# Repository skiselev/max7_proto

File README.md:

# MAX7 Proto
Prototyping Board for Altera MAX7000 CPLDs

## Table of Content
* [Introduction](#introduction)
* [Hardware Documentation](#hardware-documentation)
  * [Schematic and PCB Layout](#schematic-and-pcb-layout)
  * [Connectors and Jumpers](#connectors-and-jumpers)
  * [Bill of Materials](#bill-of-materials)
* [Programming](#programming)

## Introduction

MAX7 Proto is a prototyping board based on Altera MAX7000 series CPLDs. The board has pin headers on both sides, and it can be easily mounted on a breadboard. It also includes a 3.3V LDO, so that MAX7000AE CPLDs can be used. A DIP-8 oscillator socket is provided for the designs that requre a clock.

## Hardware Documentation

### Schematic and PCB Layout

[Schematic](KiCad/MAX7_Proto-Schematic.pdf)

[PCB Layout](KiCad/MAX7_Proto-Board.pdf)

### Connectors and Jumpers

#### J1, J2 - CPLD Breakout Pin Headers
Pin   | Signal Name | Description               | Pin   | Signal Name | Description
----- | ----------- | ------------------------- | ----- | ----------- | -------------------------
J1-1  | VCC         | Power Supply - +5V        | J2-1  | VCC         | Power Supply - +5V
J1-2  | PIN1_TDI    | CPLD Pin 1; JTAG TDI; I/O | J2-2  | PIN44       | CPLD Pin 44; I/O
J1-3  | PIN2        | CPLD Pin 2; I/O           | J2-3  | PIN43       | CPLD Pin 43; I/O
J1-4  | PIN3        | CPLD Pin 3; I/O           | J2-4  | PIN42       | CPLD Pin 42; I/O
J1-5  | PIN5        | CPLD Pin 5; I/O           | J2-5  | PIN40       | CPLD Pin 40; In, OE2, GCLK2
J1-6  | PIN6        | CPLD Pin 6; I/O           | J2-6  | PIN39       | CPLD Pin 39; In, GCLRn
J1-7  | PIN7_TMS    | CPLD Pin 7; JTAG TMS; I/O | J2-7  | PIN38       | CPLD Pin 38; In, OE1n
J1-8  | PIN8        | CPLD Pin 8; I/O           | J2-8  | PIN37       | CPLD Pin 37; In, GCLK2
J1-9  | PIN10       | CPLD Pin 10; I/O          | J2-9  | PIN35       | CPLD Pin 35; I/O
J1-10 | PIN11       | CPLD Pin 11; I/O          | J2-10 | PIN34       | CPLD Pin 34; I/O
J1-11 | PIN12       | CPLD Pin 12; I/O          | J2-11 | PIN33       | CPLD Pin 33; I/O
J1-12 | PIN13       | CPLD Pin 13; I/O          | J2-12 | PIN32_TDO   | CPLD Pin 32; JTAG TDO; I/O
J1-13 | PIN14       | CPLD Pin 14; I/O          | J2-13 | PIN31       | CPLD Pin 31; I/O
J1-14 | PIN15       | CPLD Pin 15; I/O          | J2-14 | PIN30       | CPLD Pin 30; I/O
J1-15 | PIN18       | CPLD Pin 18; I/O          | J2-15 | PIN28       | CPLD Pin 28; I/O
J1-16 | PIN19       | CPLD Pin 19; I/O          | J2-16 | PIN27       | CPLD Pin 27; I/O
J1-17 | PIN20       | CPLD Pin 20; I/O          | J2-17 | PIN26_TCK   | CPLD Pin 26; JTAG TCK; I/O
J1-18 | PIN21       | CPLD Pin 21; I/O          | J2-18 | PIN25       | CPLD Pin 25; I/O
J1-19 | PIN22       | CPLD Pin 22; I/O          | J2-19 | PIN23       | CPLD Pin 23; I/O
J1-20 | GND         | Ground                    | J2-20 | GND         | Ground

#### J3 - JTAG - CPLD
Pin  | Signal Name | Description      | Pin  | Signal Name | Description
---- | ----------- | ---------------- | ---- | ---------- | ----------------
1    | TCK         | Test Clock       | 2    | GND         | Ground
3    | TDO         | Test Data Output | 4    | 3.3V        | Power Supply - +3.3V
5    | TMS         | Test Mode Select | 6    | PIN2        | No Connect
7    | NC          | No Connect       | 8    | NC          | No Connect
9    | TDI         | Test Data Input  | 10   | GND         | Ground

#### JP1 - LDO Bypass
Solder instead of U2 LDO when using a 5V CPLD

#### JP2 - Oscillator Connect
Solder to connect X1 oscillator to CPLD pin 37 / GCLK1

### Bill of Materials

[MAX7_Proto project on Mouser.com](https://www.mouser.com/ProjectManager/ProjectDetail.aspx?AccessID=f840bea3ac) - View and order all components except of the PCB.

[MAX7_Proto project on OSH Park](https://oshpark.com/shared_projects/AL0pME1G) - View and order the PCB.

Component type     | Reference | Description                                 | Quantity | Possible sources and notes 
------------------ | --------- | ------------------------------------------- | -------- | --------------------------
PCB                |           | MAX7 Proto PCB                              | 1        | Order from a PCB manufacturer of your choice using provided Gerber or KiCad files
Capacitor          | C1        | 10nF	0603 SMT                               | 1        | Mouser [77-V0603Y103KXJAC31X](https://www.mouser.com/ProductDetail/77-V0603Y103KXJAC31X)
Capacitor          | C2 - C7   | 100nF 0603 SMT                              | 6        | Mouser [77-VJ0603Y104JXJPBC](https://www.mouser.com/ProductDetail/77-VJ0603Y104JXJPBC)
Capacitor          | C8, C9    | 10uF	1210 SMT                               | 2        | Mouser [74-593D106X9016A2TE3](https://www.mouser.com/ProductDetail/74-593D106X9016A2TE3)
LED                | D1        | 0603 SMT Power/Green                        | 1        | Mouser [78-VLMG1300-GS08](https://www.mouser.com/ProductDetail/78-VLMG1300-GS08)
Connector          | J1, J2    | Pin Header 1x20, 2.54 mm pitch              | 2        | Mouser [649-68000-220HLF](https://www.mouser.com/ProductDetail/649-68000-220HLF)
Connector          | J5        | Pin Header 2x5, 2.54 mm pitch, Shrouded     | 1        | Mouser [710-61201021621](https://www.mouser.com/ProductDetail/710-61201021621)
Resistor           | R1        | 1 kOhm 0603 SMT                             | 1        | Mouser [71-CRCW0603-1.0K-E3](https://www.mouser.com/ProductDetail/71-CRCW0603-1.0K-E3)
Resistor           | R2 - R5   | 10 kOhm 0603 SMT                            | 4        | Mouser [71-CRCW0603-10K-E3](https://www.mouser.com/ProductDetail/71-CRCW0603-10K-E3) 
Integrated Circuit | U1        | EPM7064AETC44, Altera MAX 7000AE CPLD, TQFP-44 | 1     | Mouser [989-EPM7064AETC4410N](https://www.mouser.com/ProductDetail/989-EPM7064AETC4410N)
Integrated Circuit | U2        | TPS79333-EP                                 | 1        | Mouser [595-TPS79333DBVR](https://www.mouser.com/ProductDetail/595-TPS79333DBVR)
Socket             | X1        | Half can / DIP-8 Oscillator Socket          | 1        | Mouser [535-1108800](https://www.mouser.com/ProductDetail/535-1108800)
Crystal Oscillator | X1        | Half can / DIP-8 Oscillator, 5V             | 1        | Optional, frequency depends on the design requirements

## Programming

Use free Altera Quartus II 13.0sp1 Web Edition to program the CPLD. Newer Quartus versions do not support Altera MAX7000 CPLDs.

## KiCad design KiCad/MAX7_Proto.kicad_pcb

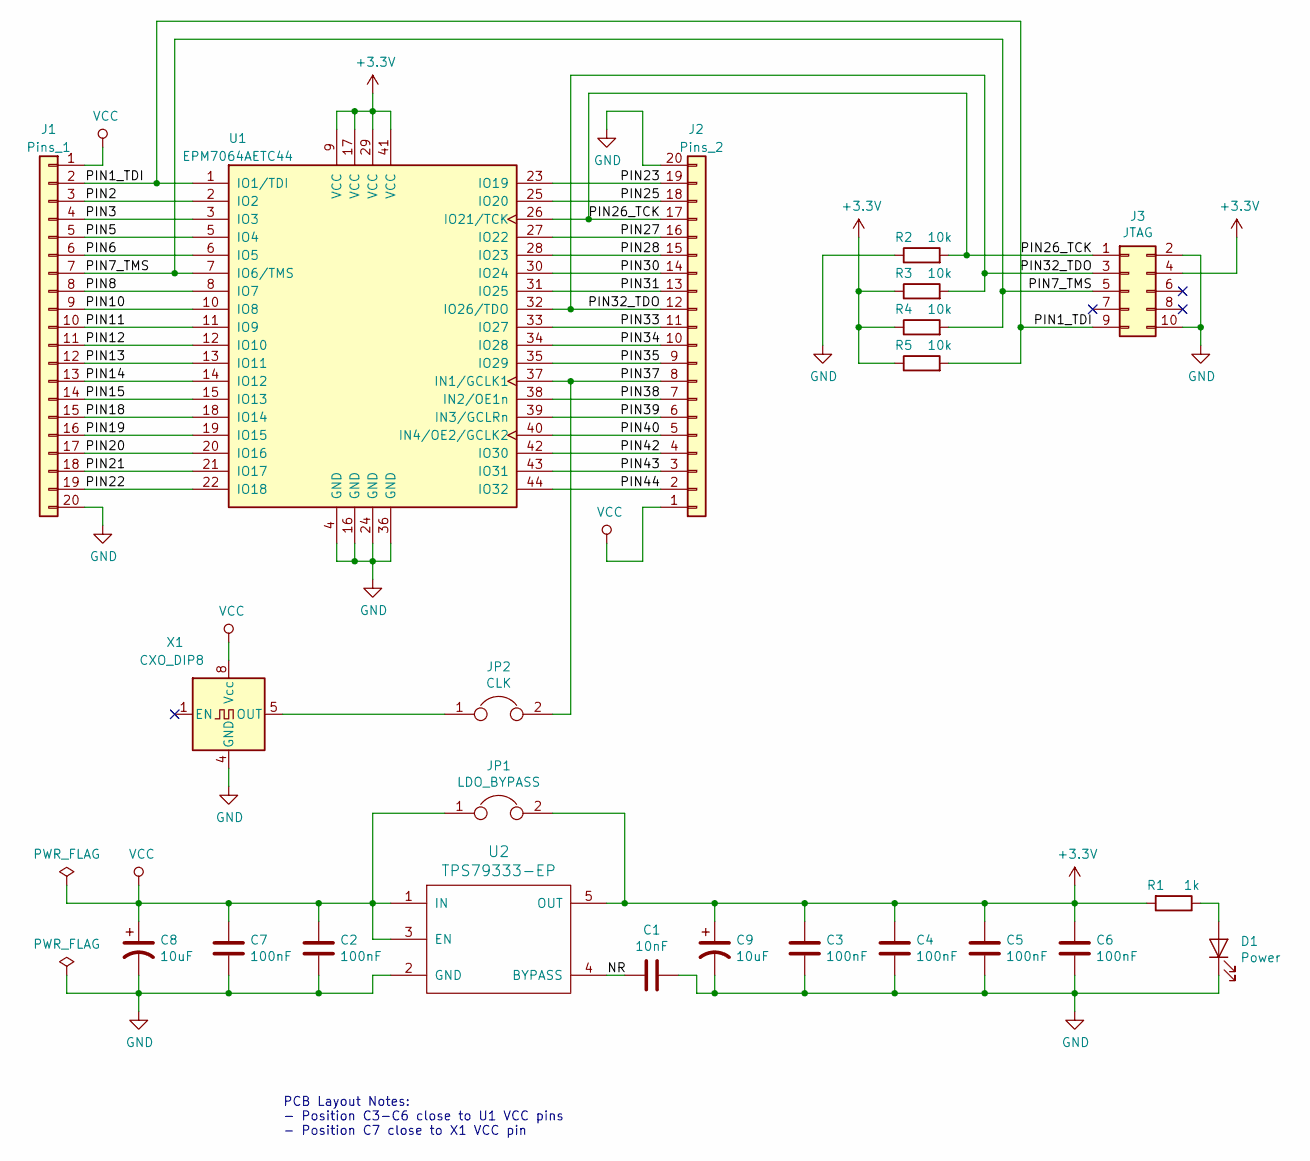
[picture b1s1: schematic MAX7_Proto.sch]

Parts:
C1: 10nF; C_0603_1608Metric_Pad1.05x0.95mm_HandSolder
C2, C3, C4, C5, C6, C7: 100nF; C_0603_1608Metric_Pad1.05x0.95mm_HandSolder
C8, C9: 10uF; CP_EIA-3216-10_Kemet-I_Pad1.58x1.35mm_HandSolder
D1: Power; LED_0603_1608Metric_Pad1.05x0.95mm_HandSolder
J1: Pins_1; PinHeader_1x20_P2.54mm_Vertical
J2: Pins_2; PinHeader_1x20_P2.54mm_Vertical
J3: JTAG; IDC-Header_2x05_P2.54mm_Vertical
JP1: LDO_BYPASS; SolderJumper-2_P1.3mm_Open_RoundedPad1.0x1.5mm
JP2: CLK; SolderJumper-2_P1.3mm_Open_RoundedPad1.0x1.5mm
R1: 1k; R_0603_1608Metric_Pad1.05x0.95mm_HandSolder
R2, R3, R4, R5: 10k; R_0603_1608Metric_Pad1.05x0.95mm_HandSolder
U1: EPM7064AETC44; TQFP-44_10x10mm_P0.8mm
U2: TPS79333-EP; SOT-23-5_HandSoldering
X1: CXO_DIP8; Oscillator_DIP-8

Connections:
+3V3: C3.1, C4.1, C5.1, C6.1, C9.1, J3.4, JP1.2, R1.2, R3.1, R4.1, R5.1, U1.9 (VCC), U1.17 (VCC), U1.29 (VCC), U1.41 (VCC), U2.5 (OUT)
/NR: C1.1, U2.4 (BYPASS)
/PIN1_TDI: J1.2, J3.9, R5.2, U1.1 (IO1/TDI)
/PIN2: J1.3, U1.2 (IO2)
/PIN3: J1.4, U1.3 (IO3)
/PIN5: J1.5, U1.5 (IO4)
/PIN6: J1.6, U1.6 (IO5)
/PIN7_TMS: J1.7, J3.5, R4.2, U1.7 (IO6/TMS)
/PIN8: J1.8, U1.8 (IO7)
/PIN10: J1.9, U1.10 (IO8)
/PIN11: J1.10, U1.11 (IO9)
/PIN12: J1.11, U1.12 (IO10)
/PIN13: J1.12, U1.13 (IO11)
/PIN14: J1.13, U1.14 (IO12)
/PIN15: J1.14, U1.15 (IO13)
/PIN18: J1.15, U1.18 (IO14)
/PIN19: J1.16, U1.19 (IO15)
/PIN20: J1.17, U1.20 (IO16)
/PIN21: J1.18, U1.21 (IO17)
/PIN22: J1.19, U1.22 (IO18)
/PIN23: J2.19, U1.23 (IO19)
/PIN25: J2.18, U1.25 (IO20)
/PIN26_TCK: J2.17, J3.1, R2.2, U1.26 (IO21/TCK)
/PIN27: J2.16, U1.27 (IO22)
/PIN28: J2.15, U1.28 (IO23)
/PIN30: J2.14, U1.30 (IO24)
/PIN31: J2.13, U1.31 (IO25)
/PIN32_TDO: J2.12, J3.3, R3.2, U1.32 (IO26/TDO)
/PIN33: J2.11, U1.33 (IO27)
/PIN34: J2.10, U1.34 (IO28)
/PIN35: J2.9, U1.35 (IO29)
/PIN37: J2.8, JP2.2, U1.37 (IN1/GCLK1)
/PIN38: J2.7, U1.38 (IN2/OE1n)
/PIN39: J2.6, U1.39 (IN3/GCLRn)
/PIN40: J2.5, U1.40 (IN4/OE2/GCLK2)
/PIN42: J2.4, U1.42 (IO30)
/PIN43: J2.3, U1.43 (IO31)
/PIN44: J2.2, U1.44 (IO32)
GND: C1.2, C2.2, C3.2, C4.2, C5.2, C6.2, C7.2, C8.2, C9.2, D1.1 (K), J1.20, J2.20, J3.2, J3.10, R2.1, U1.4 (GND), U1.16 (GND), U1.24 (GND), U1.36 (GND), U2.2 (GND), X1.4 (GND)
unnamed: D1.2 (A), R1.1
unnamed: JP2.1, X1.5 (OUT)
VCC: C2.1, C7.1, C8.1, J1.1, J2.1, JP1.1, U2.1 (IN), U2.3 (EN), X1.8 (Vcc)

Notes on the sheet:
PCB Layout Notes: - Position C3-C6 close to U1 VCC pins - Position C7 close to X1 VCC pin

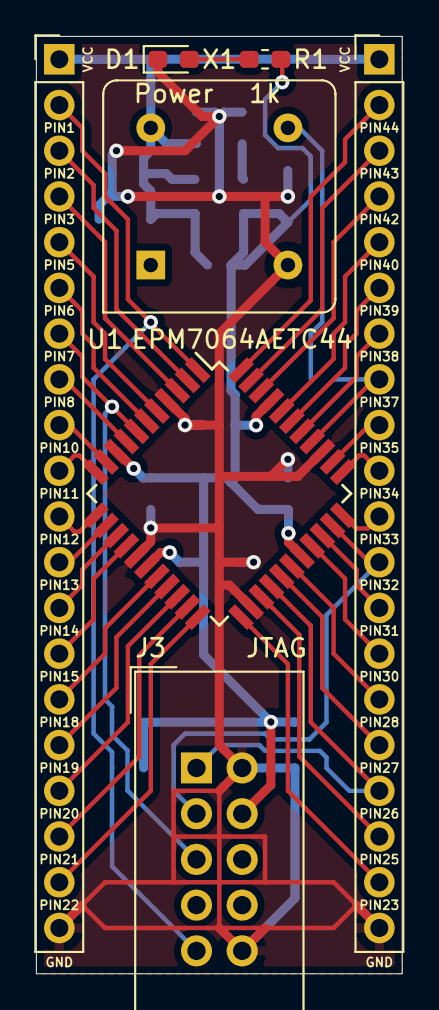
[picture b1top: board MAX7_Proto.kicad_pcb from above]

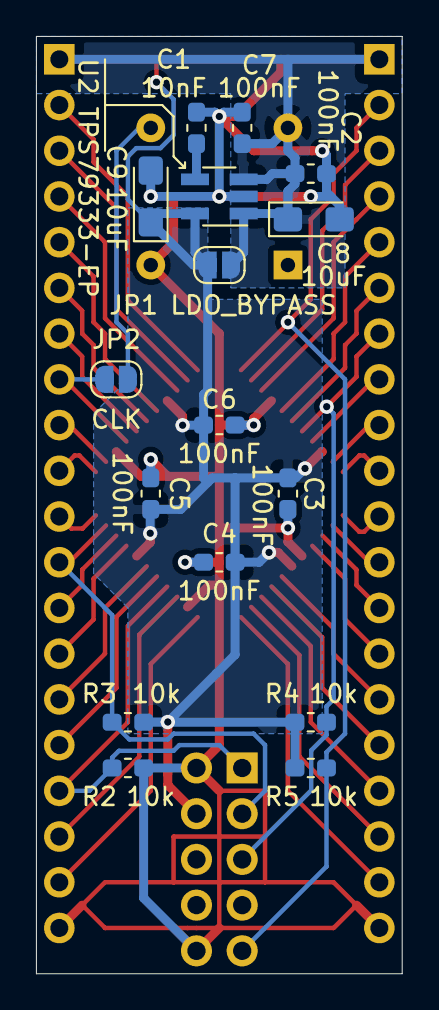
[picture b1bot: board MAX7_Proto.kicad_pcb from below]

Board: 2 copper layers, 20.3 x 52.1 mm, 23 parts (16 on the bottom side), 42 nets.

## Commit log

2020-08-07 Add design files
2020-08-07 README: Add content
2020-08-07 README: Fix typos
